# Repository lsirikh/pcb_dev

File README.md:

# PCB Development Archive

KiCad 회로도와 PCB 설계 실습, 미세먼지 장치 보드 자료를 모은 저장소입니다. 소프트웨어 실행 프로젝트가 아니라 회로·보드 설계 파일을 보관합니다.

## 구성

- `2044-breadboard-power`: 전원 보드 설계 자료
- `2045-test`부터 `2050-eeprom`까지: 풋프린트, 오디오, 네트, 다층·다중 시트 등 실습 자료
- `microdust_pcb`: 미세먼지 장치 관련 보드
- `library`: 부품 라이브러리

## 열어보기

프로젝트별 `.pro`, `.sch`, `.kicad_pcb`를 지원하는 KiCad 환경에서 확인합니다. 오래된 형식과 백업 파일이 함께 있으므로 원본을 보존한 사본에서 변환하는 편이 좋습니다. 부품 라이브러리 경로도 확인해야 합니다.

파일 보관 자체가 제작 검증이나 양산 가능성을 뜻하지는 않습니다. 실습과 장치 설계 자료를 구분해 참고하세요.

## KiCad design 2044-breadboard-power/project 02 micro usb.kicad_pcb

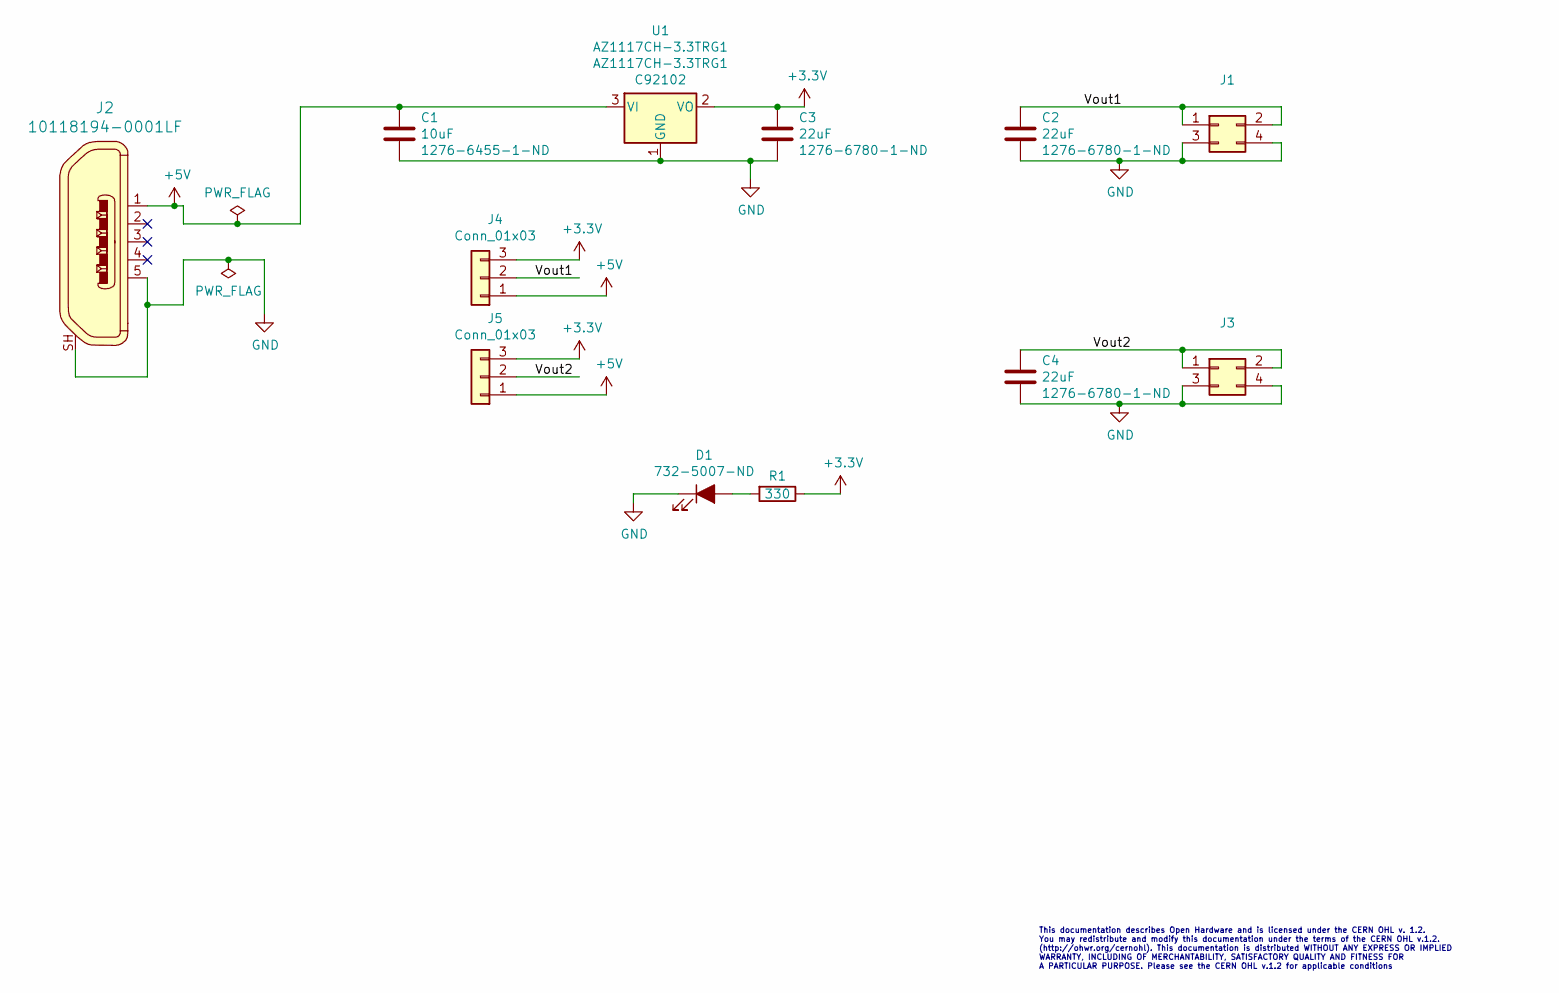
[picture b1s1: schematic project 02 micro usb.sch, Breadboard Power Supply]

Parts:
C1: 10uF; C_0805_2012Metric_Pad1.15x1.40mm_HandSolder; Manufacture Part Number CL21A106KOQNNNG; Digikey 1276-6455-1-ND
C2, C3, C4: 22uF; C_0805_2012Metric_Pad1.15x1.40mm_HandSolder; Manufacture Part Number CL21A226MOCLRNC; Digikey 1276-6780-1-ND
D1: LED_ALT; LED_D3.0mm; Digikey 732-5007-ND
J1, J3: Conn_02x02_Odd_Even; PinHeader_2x02_P2.54mm_Vertical
J2: 10118194-0001LF; USB_Micro_B_Female_10118194-0001LF; MPN 10118194-0001LF; Digi-Key_PN 609-4618-1-ND
J4, J5: Conn_01x03; PinHeader_1x03_P2.54mm_Vertical
R1: 330; R_0805_2012Metric_Pad1.15x1.40mm_HandSolder
U1: AZ1117CH-3.3TRG1; SOT-223-3_TabPin2; Digikey AZ1117CH-3.3TRG1

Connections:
+3V3: C3.1, J4.3, J5.3, R1.1, U1.2 (VO)
+5V: C1.1, J2.1, J4.1, J5.1, U1.3 (VI)
/Vout1: C2.1, J1.1, J1.2, J4.2
/Vout2: C4.1, J3.1, J3.2, J5.2
GND: C1.2, C2.2, C3.2, C4.2, D1.1 (K), J1.3, J1.4, J2.5, J2.SH, J3.3, J3.4, U1.1 (GND)
unnamed: D1.2 (A), R1.2

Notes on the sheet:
This documentation describes Open Hardware and is licensed under the CERN OHL v. 1.2. You may redistribute and modify this documentation under the terms of the CERN OHL v.1.2. (http://ohwr.org/cernohl). This documentation is distributed WITHOUT ANY EXPRESS OR IMPLIED WARRANTY, INCLUDING OF MERCHANT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

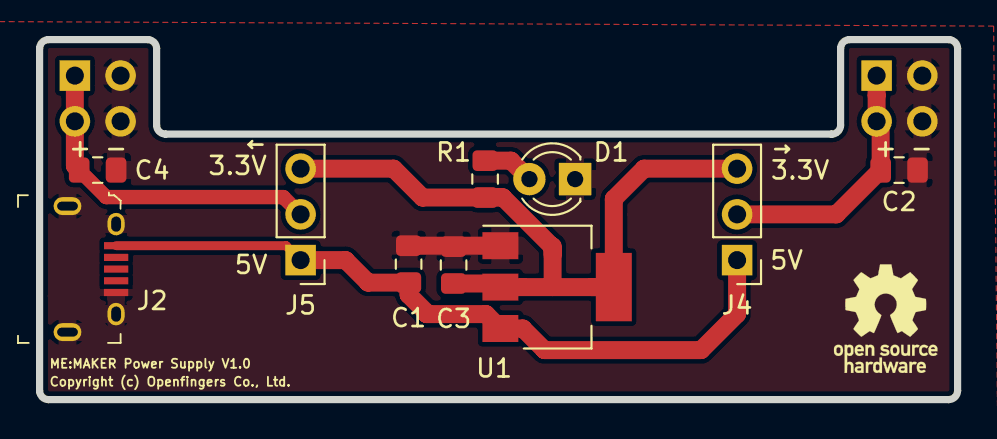
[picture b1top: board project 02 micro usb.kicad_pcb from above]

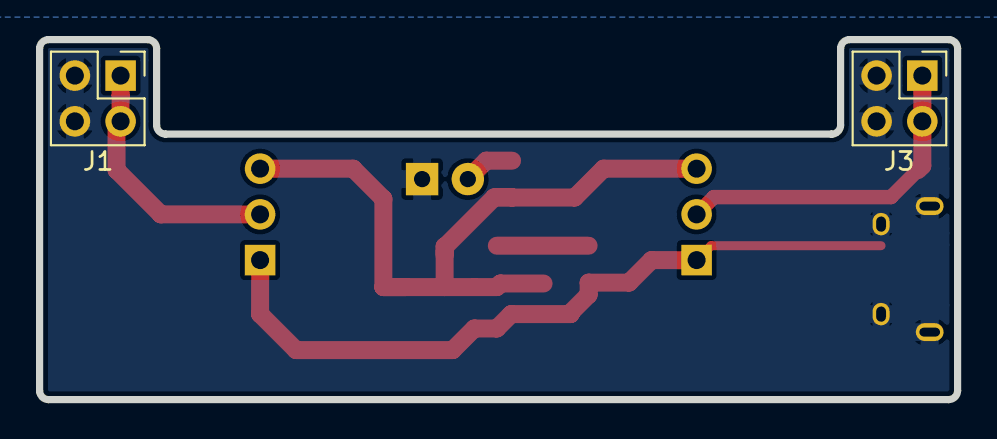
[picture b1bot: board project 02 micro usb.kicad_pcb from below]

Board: 2 copper layers, 51.0 x 20.0 mm, 12 parts (2 on the bottom side), 6 nets.

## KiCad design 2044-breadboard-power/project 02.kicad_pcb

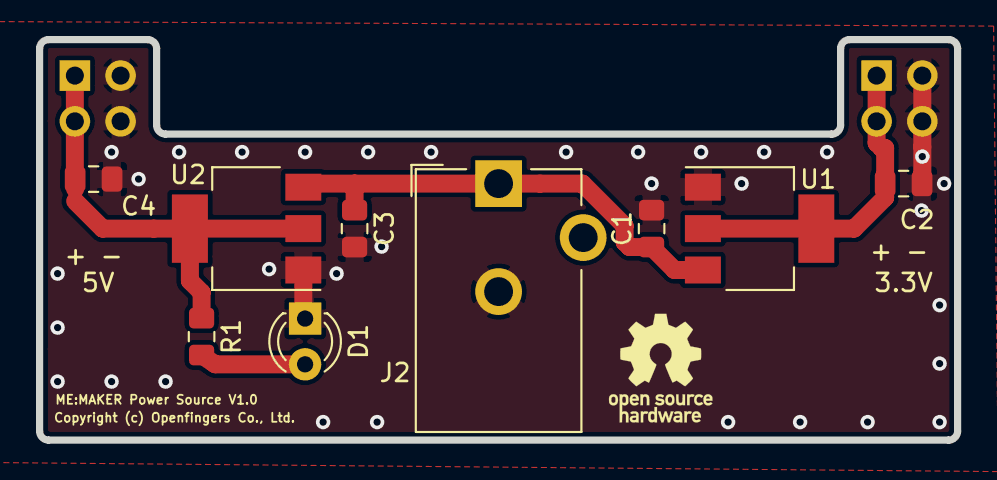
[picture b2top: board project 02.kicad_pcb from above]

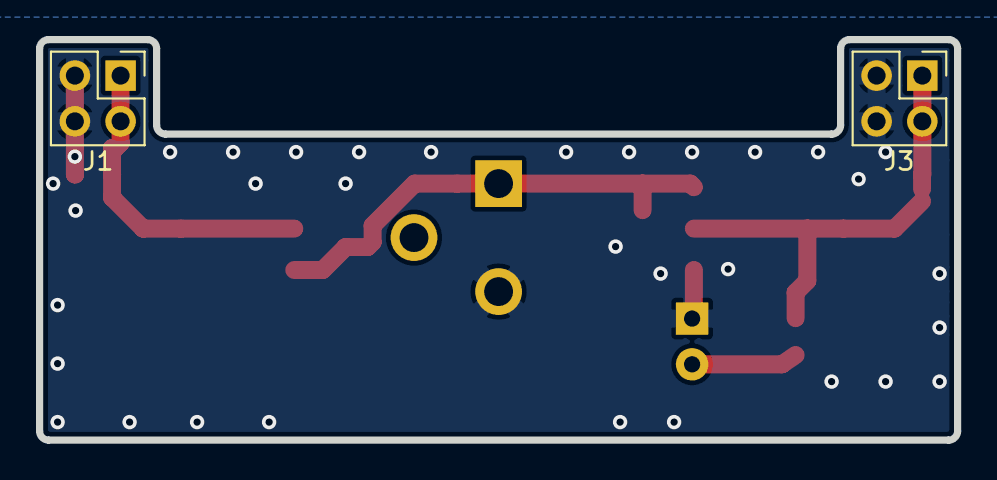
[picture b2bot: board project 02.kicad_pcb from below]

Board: 2 copper layers, 51.0 x 22.2 mm, 11 parts (2 on the bottom side), 5 nets.

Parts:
C1, C3: 10uF; C_0805_2012Metric_Pad1.15x1.40mm_HandSolder
C2, C4: 22uF; C_0805_2012Metric_Pad1.15x1.40mm_HandSolder
D1: LED_ALT; LED_D3.0mm
J1, J3: Conn_02x02_Odd_Even; PinHeader_2x02_P2.54mm_Vertical
J2: Barrel_Jack; BarrelJack_CUI_PJ-102AH_Horizontal
R1: 1K; R_0805_2012Metric_Pad1.15x1.40mm_HandSolder
U1: AZ1117CH-3.3TRG1; SOT-223-3_TabPin2
U2: AZ1117CH-5.0TRG1; SOT-223-3_TabPin2

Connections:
GND: C1.2, C2.2, C3.2, C4.2, D1.1, J1.3, J1.4, J2.2, J3.3, J3.4, U1.1, U2.1
unnamed: C1.1, C3.1, J2.1, U1.3, U2.3
unnamed: C2.1, J1.1, J1.2, U1.2
unnamed: C4.1, J3.1, J3.2, R1.1, U2.2
unnamed: D1.2, R1.2

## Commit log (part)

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2019-10-12 first init

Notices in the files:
2044-breadboard-power/project 02 micro usb.kicad_pcb:
Copyright (c) Openfingers Co., Ltd.
